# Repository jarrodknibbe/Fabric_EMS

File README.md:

# Temera - EMS eTextile Shield for Teensy

TL;DR - A custom board and code for integrating electronics (especially EMS) into fabric garments.

Temera is a soft, finnles, Sleeper Ray, with paired electric organs. Temera is also a platform for creating soft circuits with paired EMS stimulation outputs.

Specifically, Temera is a prototype two-channel EMS shield, designed to be easily incorporated into fabrics.
16 GPIO that can be set to Analog Input as well as 2 Channels of EMS are broken out. In addition to pins, we added holes, so that each channel can easily be connected to using conductive thread. 

This is an early prototype that is still under active development. More details to follow.

Code:

The driver code is available in this repository as well. The stable implementation provides all of the basic code to get you started. There is also a 'dev_code' version of the code available, where we continue to play with further developments. (We recommend using the stable implementation, at least until you are comfortable with its operation).

Work from the Run_EMS.ino file. This handles the board and the EMS signal generation. The signal generation works through a series of timers handled by the Teensy. There are individual timers per channel frequency and pulse width. Per channel, a frequency timer ticks along at the desired frequency of stimulation. This frequency timer then handles triggering the pulse width timer to run, so that each pulse of EMS is the correct shape / length. 

DEV_Code changes:
+ Basic sensor integration outline - stim if some sensor value between x and y
+ Change potentiometer to work constantly when in manual update mode 

(Worth noting, Teensys are more stable on Windows than on a Mac).

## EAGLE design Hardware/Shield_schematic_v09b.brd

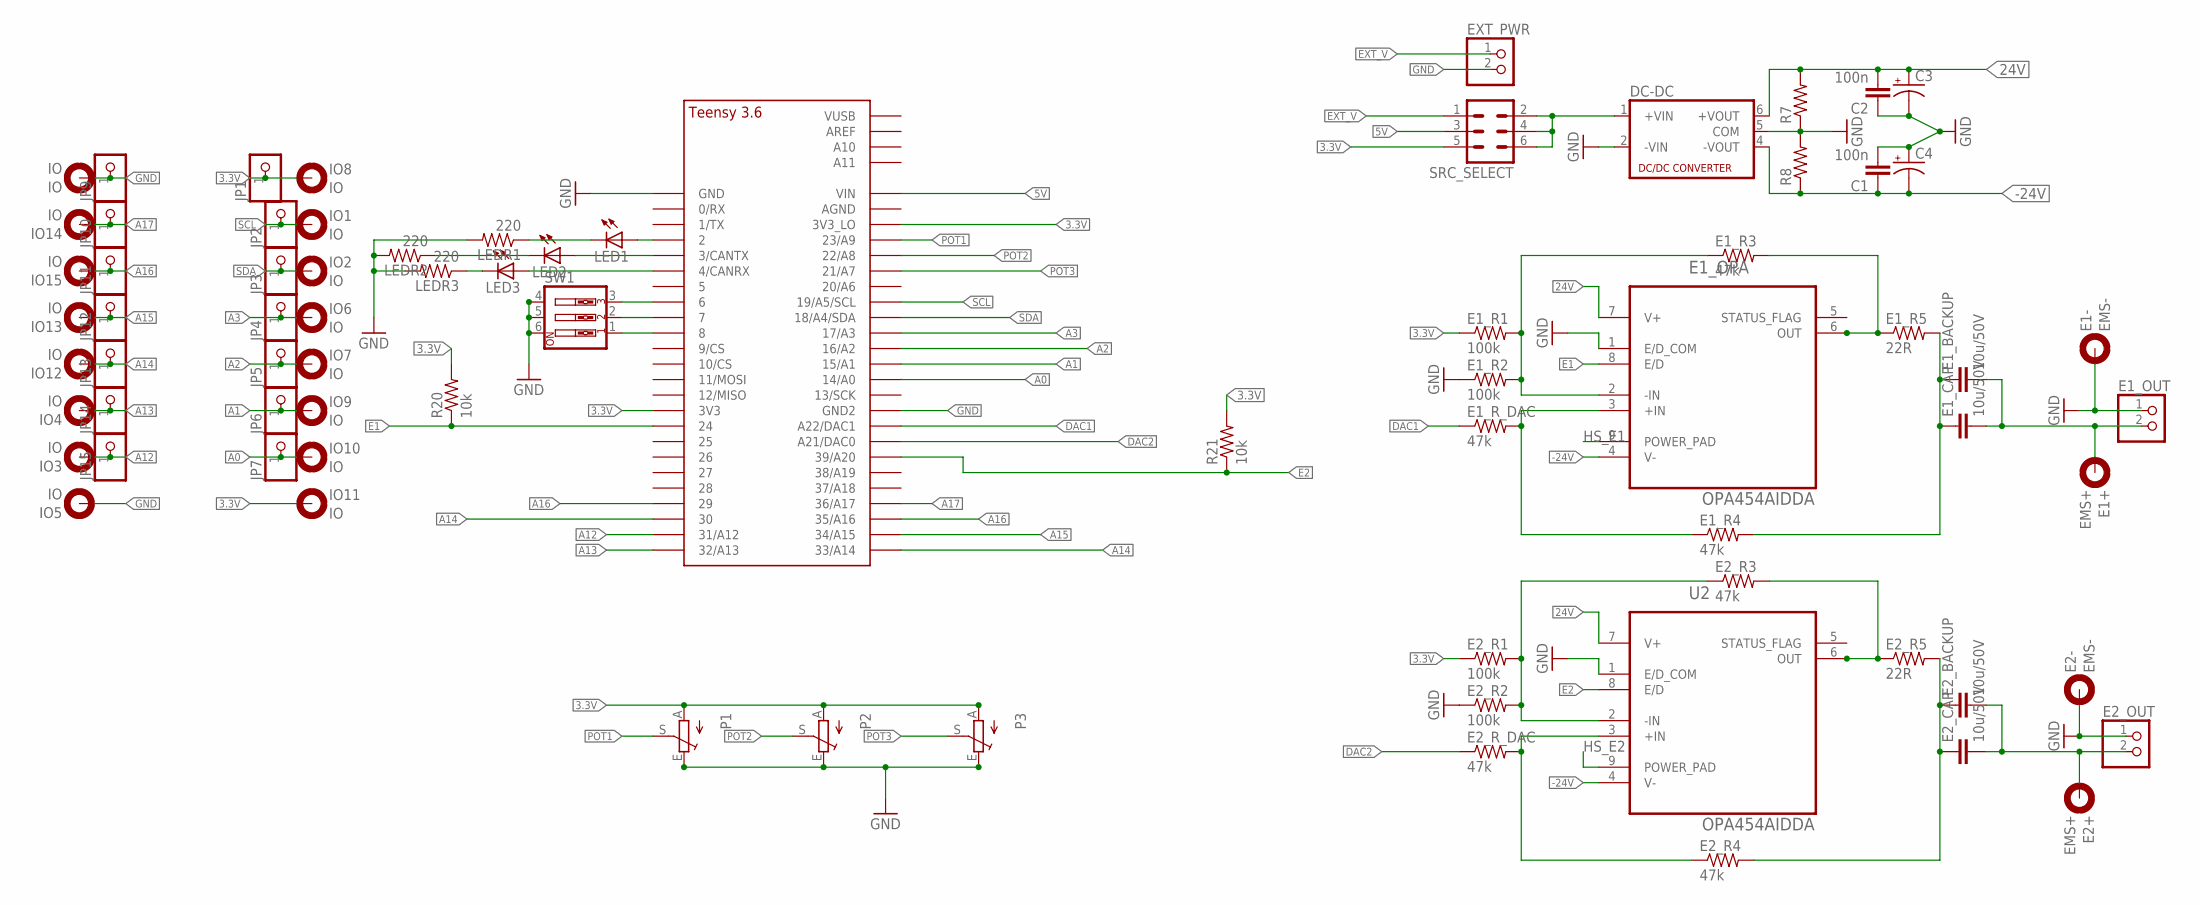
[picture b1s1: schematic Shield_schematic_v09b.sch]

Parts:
C1, C2: 100n; 1206
C3, C4: CPOL-USE2.5-5; E2,5-5
DC-DC: NMA
E1+, E2+: EMS+; 4,1-PAD
E1-, E2-: EMS-; 4,1-PAD
E1_BACKUP, E2_BACKUP: 10u/50V; CAP-PTH-5MM
E1_CAP, E2_CAP: 10u/50V; 1206
E1_OPA: OPA454AIDDA; SOIC127P600X170-9N
E1_OUT, E2_OUT: PINHD-1X2; 1X02
E1_R1, E1_R2, E2_R1, E2_R2: 100k; 1206
E1_R3, E1_R4, E1_R_DAC, E2_R3, E2_R4, E2_R_DAC: 47k; 1206
E1_R5, E2_R5: 22R; 1206
EXT_PWR: PINHD-1X2; 1X02
IO, IO1, IO2, IO3, IO4, IO5, IO6, IO7, IO8, IO9, IO10, IO11, IO12, IO13, IO14, IO15: IO; 2,8-PAD
JP1, JP2, JP3, JP4, JP5, JP6, JP7, JP9, JP10, JP11, JP12, JP13, JP14, JP15: PINHD-1X1; 1X01
LED1, LED2, LED3: LEDCHIPLED_0805; CHIPLED_0805
LEDR1, LEDR2, LEDR3: 220; 1206
P1, P2, P3: TRIM_EU-B25P; B25P
R7, R8: RESISTORKIT; AXIAL-0.3-KIT
R20, R21: 10k; 1206
SRC_SELECT: MA03-2
SW1: SW_DIP-3; EDG-03
U2: OPA454AIDDA; SOIC127P600X170-9N
U$1: TEENSY_3.5/3.6_BASIC

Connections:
3.3V: E1_R1.1, E2_R1.1, IO8.B2,8, IO11.B2,8, JP1.1, P1.A, P2.A, P3.A, R20.2, R21.2, SRC_SELECT.5, U$1.3V3, U$1.3V3_LO
5V: SRC_SELECT.3, U$1.VIN
24V: C2.2, C3.+, DC-DC.6 (+VOUT), E1_OPA.7 (V+), R7.P$2 (2), U2.7 (V+)
-24V: C1.1, C4.-, DC-DC.4 (-VOUT), E1_OPA.4 (V-), R8.P$1 (1), U2.4 (V-)
A0: IO10.B2,8, JP7.1, U$1.14/A0
A1: IO9.B2,8, JP6.1, U$1.15/A1
A2: IO7.B2,8, JP5.1, U$1.16/A2
A3: IO6.B2,8, JP4.1, U$1.17/A3
A12: IO3.B2,8, JP15.1, U$1.31/A12
A13: IO4.B2,8, JP14.1, U$1.32/A13
A14: IO12.B2,8, JP13.1, U$1.30, U$1.33/A14
A15: IO13.B2,8, JP12.1, U$1.34/A15
A16: IO15.B2,8, JP11.1, U$1.29, U$1.35/A16
A17: IO14.B2,8, JP10.1, U$1.36/A17
DAC1: E1_R_DAC.1, U$1.A22/DAC1
DAC2: E2_R_DAC.1, U$1.21/DAC0 (A21/DAC0)
E1: E1_OPA.8 (E/D), R20.1, U$1.24
E1+: E1+.B4,1, E1_BACKUP.2, E1_CAP.2, E1_OUT.2
E2: R21.1, U2.8 (E/D), U$1.39/A20
E2+: E2+.B4,1, E2_BACKUP.2, E2_CAP.2, E2_OUT.2
EXT_V: EXT_PWR.1, SRC_SELECT.1
GND: C1.2, C2.1, C3.-, C4.+, DC-DC.2 (-VIN), DC-DC.5 (COM), E1-.B4,1, E1_OPA.1 (E/D_COM), E1_OUT.1, E1_R2.1, E2-.B4,1, E2_OUT.1, E2_R2.1, EXT_PWR.2, IO.B2,8, IO5.B2,8, JP9.1, LEDR1.2, LEDR2.2, LEDR3.2, P1.E, P2.E, P3.E, R7.P$1 (1), R8.P$2 (2), SW1.4, SW1.5, SW1.6, U2.1 (E/D_COM), U$1.GND, U$1.GND2
HS_E1: E1_OPA.9 (POWER_PAD)
HS_E2: U2.9 (POWER_PAD)
unnamed: SW1.1, U$1.8
unnamed: E1_OPA.3 (+IN), E1_R4.1, E1_R_DAC.2
unnamed: E1_BACKUP.1, E1_CAP.1, E1_R4.2, E1_R5.2
unnamed: LED1.A, U$1.2
unnamed: E1_OPA.6 (OUT), E1_R3.2, E1_R5.1
unnamed: SW1.2, U$1.7
unnamed: E1_OPA.2 (-IN), E1_R1.2, E1_R2.2, E1_R3.1
unnamed: SW1.3, U$1.6
unnamed: E2_R4.1, E2_R_DAC.2, U2.3 (+IN)
unnamed: E2_BACKUP.1, E2_CAP.1, E2_R4.2, E2_R5.2
unnamed: LED2.A, U$1.3/CANTX
unnamed: E2_R3.2, E2_R5.1, U2.6 (OUT)
unnamed: LED3.A, U$1.4/CANRX
unnamed: E2_R1.2, E2_R2.2, E2_R3.1, U2.2 (-IN)
unnamed: LED1.C, LEDR1.1
unnamed: DC-DC.1 (+VIN), SRC_SELECT.2, SRC_SELECT.4, SRC_SELECT.6
unnamed: LED2.C, LEDR2.1
unnamed: LED3.C, LEDR3.1
POT1: P1.S, U$1.23/A9
POT2: P2.S, U$1.22/A8
POT3: P3.S, U$1.21/A7
SCL: IO1.B2,8, JP2.1, U$1.19/A5/SCL
SDA: IO2.B2,8, JP3.1, U$1.18/A4/SDA

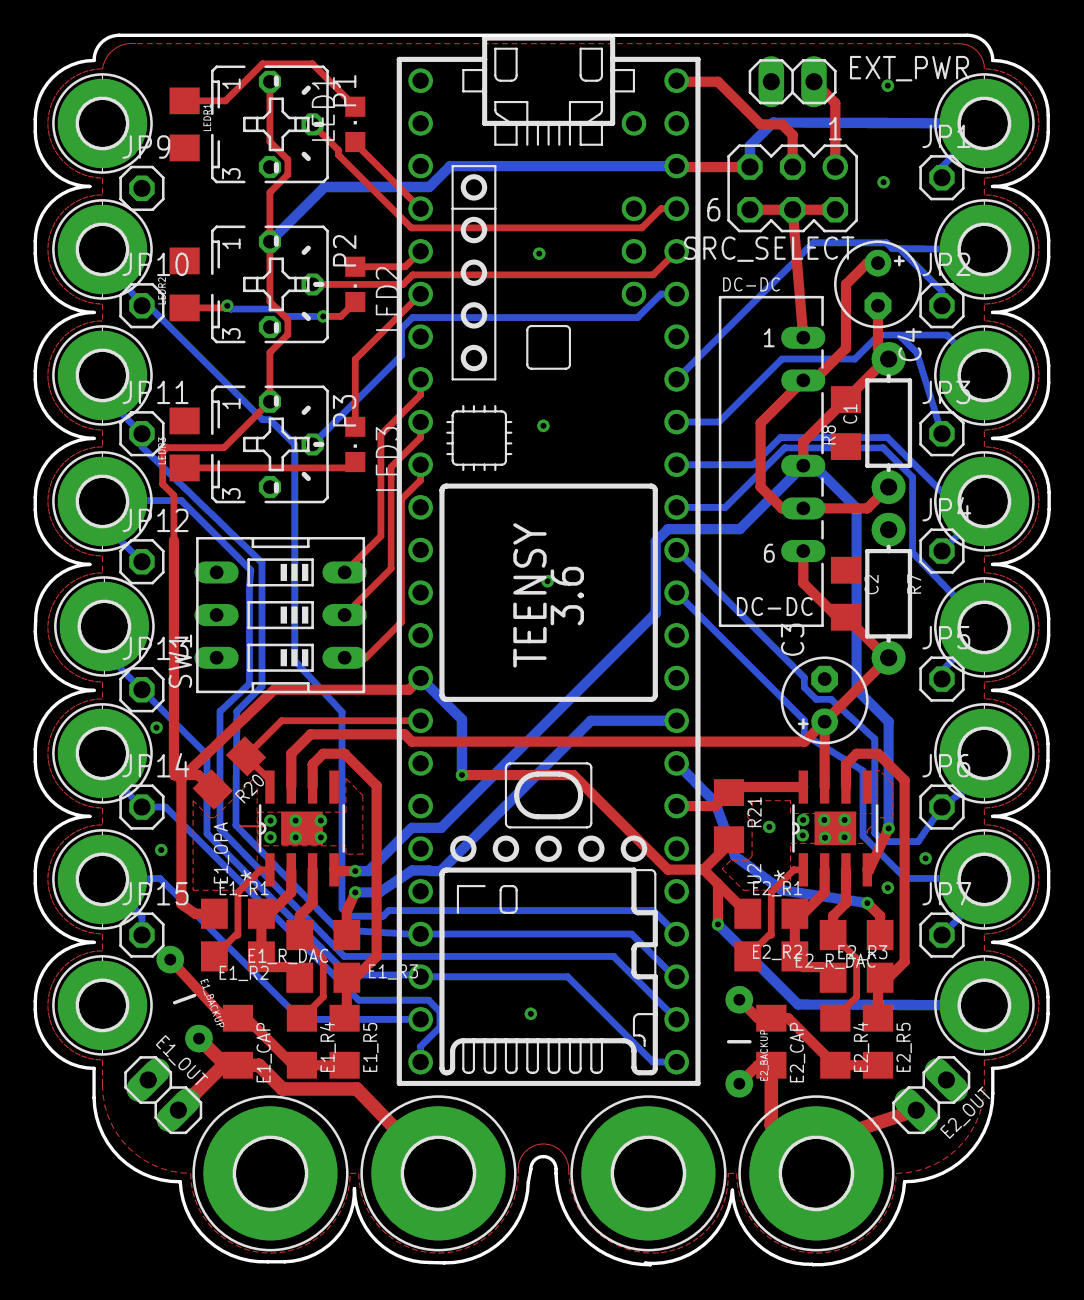
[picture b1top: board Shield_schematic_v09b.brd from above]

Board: 2 copper layers, 60.4 x 73.2 mm, 76 parts (0 on the bottom side), 45 nets.

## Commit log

2018-03-16 Initial upload of all files
2018-03-16 updated Readme with more background info
2018-03-25 eagle files + partlist
2018-04-27 Updated Readme, separated stable and development code branches
2018-04-27 added serial command control to stable code
2018-05-07 mainly fixed UI related things
    changed the pot behavior so its more intuitive, made the debug information clearer.
2018-05-07 making it less noisy
    I was getting too many channel updates, so I increased the threshold by turning >= to just > .
    This is a lazy fix. Should use some sort of filtering instead.
2022-03-21 added new channel label
    added channel label that pulses EMS stimulation to give 30 individual finger actuations at a set freq,wd,pw,amp.
    Also updated EMSchannel to check if EMSstimulate = true

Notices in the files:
parts and their libraries:
SparkFun-Capacitors: Licensing: Creative Commons ShareAlike 4.0 International - https://creativecommons.org/licenses/by-sa/4.0
